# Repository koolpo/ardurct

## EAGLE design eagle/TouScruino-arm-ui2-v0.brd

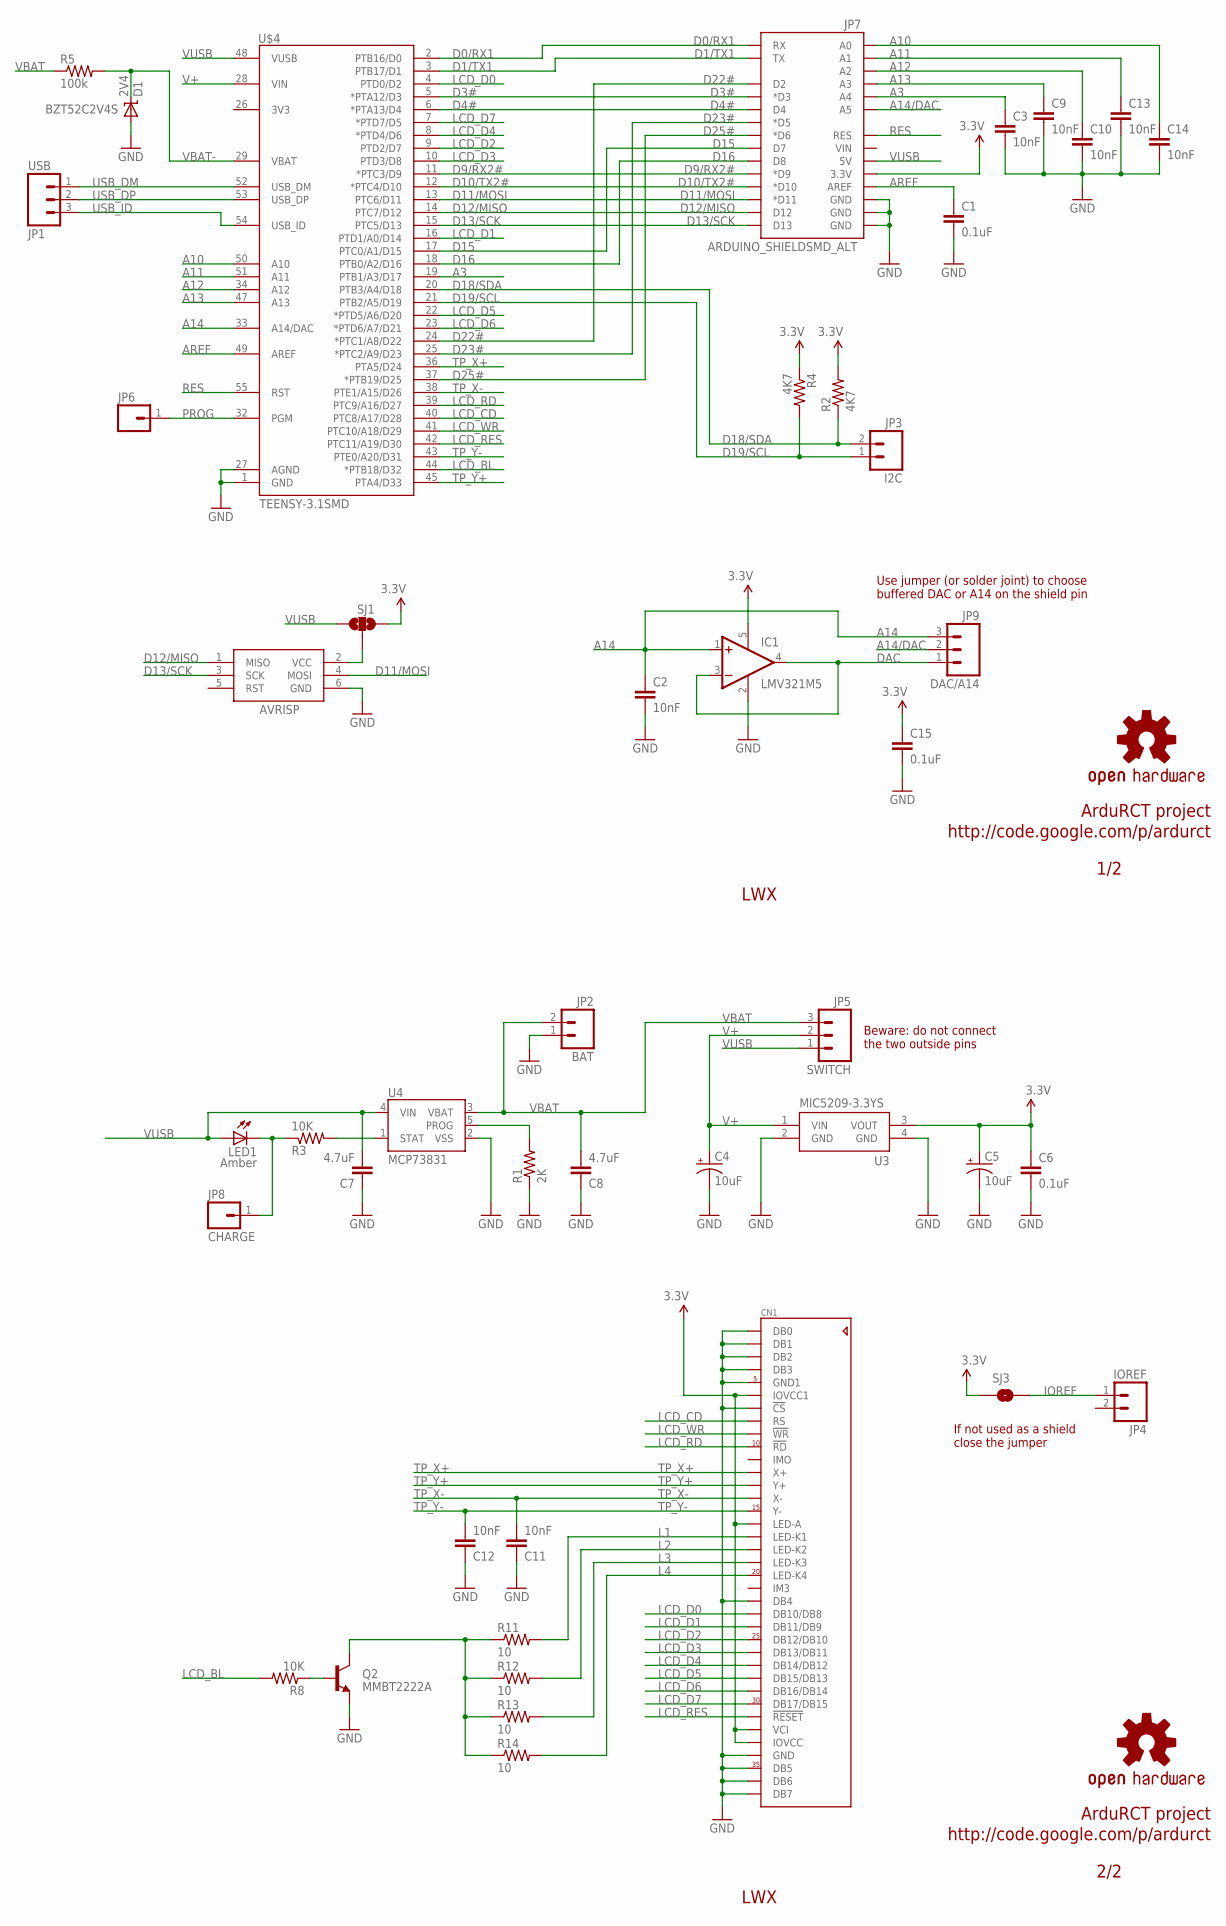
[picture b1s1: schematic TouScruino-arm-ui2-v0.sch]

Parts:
AVRISP: AVRISP; 2X3_SMD
C1, C6, C15: 0.1uF; 0805
C2, C3, C9, C10, C11, C12, C13, C14: 10nF; 0805
C4, C5: 10uF; EIA3216
C7, C8: 4.7uF; 0805
CN1: ILI9325_LCD1.0MM; ILI9325_28INCH_TS
D1: 2V4; SOD-323
IC1: LMV321M5; SOT23-5
JP1: USB; 1X03_SMD_ALT
JP2: BAT; JST-2-SMD
JP3: I2C; 1X02_SMD_ALT
JP4: IOREF; 1X02_SMD_ALT
JP5: SWITCH; 1X03_SMD_TH
JP6: M01SMD_TH; 1X01_SMD_TH
JP7: ARDUINO_SHIELDSMD_ALT; ARDUINO_SHIELD_SMD_ALT
JP8: CHARGE; 1X01_SMD
JP9: DAC/A14; 1X03_SMD_SJ
LED1: Amber; LED
Q2: MMBT2222A; SOT23-3
R1: 2K; 0805
R2, R4: 4K7; 0805
R3, R8: 10K; 0805
R5: 100k; 0805
R11, R12, R13, R14: 10; 0805
SJ1: SJ_2WAYS
SJ3: SOLDERJUMPERNO; SJ_2S-NO
U3: MIC5209-3.3YS; SOT223
U4: MCP73831; SOT23-5
U$3, U$5: OSHW-LOGOM; OSHW-LOGO-M
U$4: TEENSY-3.1SMD; TEENSY-3.1_HSMD

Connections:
3.3V: C5.A (+), C6.1, C15.1, CN1.6 (IOVCC1), CN1.16 (LED-A), CN1.32 (VCI), CN1.33 (IOVCC), IC1.5 (V+), JP7.3.3V, R2.2, R4.1, SJ1.3, SJ3.1, U3.3 (VOUT)
A3: C3.1, JP7.A4, U$4.19 (PTB1/A3/D17)
A10: C14.1, JP7.A0, U$4.50 (A10)
A11: C13.1, JP7.A1, U$4.51 (A11)
A12: C10.1, JP7.A2, U$4.34 (A12)
A13: C9.1, JP7.A3, U$4.47 (A13)
A14: C2.1, IC1.1 (+IN), JP9.3, U$4.33 (A14/DAC)
A14/DAC: JP7.A5, JP9.2
AREF: C1.1, JP7.AREF, U$4.49 (AREF)
D0/RX1: JP7.RX, U$4.2 (PTB16/D0)
D1/TX1: JP7.TX, U$4.3 (PTB17/D1)
D3#: JP7.D3 (*D3), U$4.5 (*PTA12/D3)
D4#: JP7.D4, U$4.6 (*PTA13/D4)
D9/RX2#: JP7.D9 (*D9), U$4.11 (*PTC3/D9)
D10/TX2#: JP7.D10 (*D10), U$4.12 (*PTC4/D10)
D11/MOSI: AVRISP.4 (MOSI), JP7.D11 (*D11), U$4.13 (PTC6/D11)
D12/MISO: AVRISP.1 (MISO), JP7.D12, U$4.14 (PTC7/D12)
D13/SCK: AVRISP.3 (SCK), JP7.D13, U$4.15 (PTC5/D13)
D15: JP7.D7, U$4.17 (PTC0/A1/D15)
D16: JP7.D8, U$4.18 (PTB0/A2/D16)
D18/SDA: JP3.2, R2.1, U$4.20 (PTB3/A4/D18)
D19/SCL: JP3.1, R4.2, U$4.21 (PTB2/A5/D19)
D22#: JP7.D2, U$4.24 (*PTC1/A8/D22)
D23#: JP7.D5 (*D5), U$4.25 (*PTC2/A9/D23)
D25#: JP7.D6 (*D6), U$4.37 (*PTB19/D25)
DAC: IC1.3 (-IN), IC1.4 (OUT), JP9.1
GND: AVRISP.6 (GND), C1.2, C2.2, C3.2, C4.C (-), C5.C (-), C6.2, C7.1, C8.1, C9.2, C10.2, C11.1, C12.1, C13.2, C14.2, C15.2, CN1.1 (DB0), CN1.2 (DB1), CN1.3 (DB2), CN1.4 (DB3), CN1.5 (GND1), CN1.7 (!CS), CN1.22 (DB4), CN1.34 (GND), CN1.35 (DB5), CN1.36 (DB6), CN1.37 (DB7), D1.2 (A), IC1.2 (V-), JP2.1, JP7.GND@0 (GND), JP7.GND@1 (GND), JP7.GND@2 (GND), Q2.2 (E), R1.1, U3.2 (GND), U3.4 (GND), U4.2 (VSS), U$4.1 (GND), U$4.27 (AGND)
IOREF: JP4.1, SJ3.2
L1: CN1.17 (LED-K1), R11.2
L2: CN1.18 (LED-K2), R12.2
L3: CN1.19 (LED-K3), R13.2
L4: CN1.20 (LED-K4), R14.2
LCD_BL: R8.2, U$4.44 (*PTB18/D32)
LCD_CD: CN1.8 (RS), U$4.40 (PTC8/A17/D28)
LCD_D0: CN1.23 (DB10/DB8), U$4.4 (PTD0/D2)
LCD_D1: CN1.24 (DB11/DB9), U$4.16 (PTD1/A0/D14)
LCD_D2: CN1.25 (DB12/DB10), U$4.9 (PTD2/D7)
LCD_D3: CN1.26 (DB13/DB11), U$4.10 (PTD3/D8)
LCD_D4: CN1.27 (DB14/DB12), U$4.8 (*PTD4/D6)
LCD_D5: CN1.28 (DB15/DB13), U$4.22 (*PTD5/A6/D20)
LCD_D6: CN1.29 (DB16/DB14), U$4.23 (*PTD6/A7/D21)
LCD_D7: CN1.30 (DB17/DB15), U$4.7 (*PTD7/D5)
LCD_RD: CN1.10 (!RD), U$4.39 (PTC9/A16/D27)
LCD_RES: CN1.31 (!RESET), U$4.42 (PTC11/A19/D30)
LCD_WR: CN1.9 (!WR), U$4.41 (PTC10/A18/D29)
unnamed: AVRISP.2 (VCC), SJ1.2
unnamed: Q2.1 (B), R8.1
unnamed: Q2.3 (C), R11.1, R12.1, R13.1, R14.1
unnamed: JP8.1, LED1.C1 (C), R3.1
unnamed: R3.2, U4.1 (STAT)
unnamed: R1.2, U4.5 (PROG)
PROG: JP6.1, U$4.32 (PGM)
RES: JP7.RES, U$4.55 (RST)
TP_X+: CN1.12 (X+), U$4.36 (PTA5/D24)
TP_X-: C11.2, CN1.14 (X-), U$4.38 (PTE1/A15/D26)
TP_Y+: CN1.13 (Y+), U$4.45 (PTA4/D33)
TP_Y-: C12.2, CN1.15 (Y-), U$4.43 (PTE0/A20/D31)
USB_DM: JP1.1, U$4.52 (USB_DM)
USB_DP: JP1.2, U$4.53 (USB_DP)
USB_ID: JP1.3, U$4.54 (USB_ID)
V+: C4.A (+), JP5.2, U3.1 (VIN), U$4.28 (VIN)
VBAT: C8.2, JP2.2, JP5.3, R5.1, U4.3 (VBAT)
VBAT-: D1.1 (C), R5.2, U$4.29 (VBAT)
VUSB: C7.2, JP5.1, JP7.5V, LED1.A1 (A), SJ1.1, U4.4 (VIN), U$4.48 (VUSB)

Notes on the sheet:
LWX
1/2
2/2
Beware: do not connect the two outside pins
If not used as a shield close the jumper
ArduRCT project
http://code.google.com/p/ardurct
Use jumper (or solder joint) to choose buffered DAC or A14 on the shield pin
BZT52C2V4S

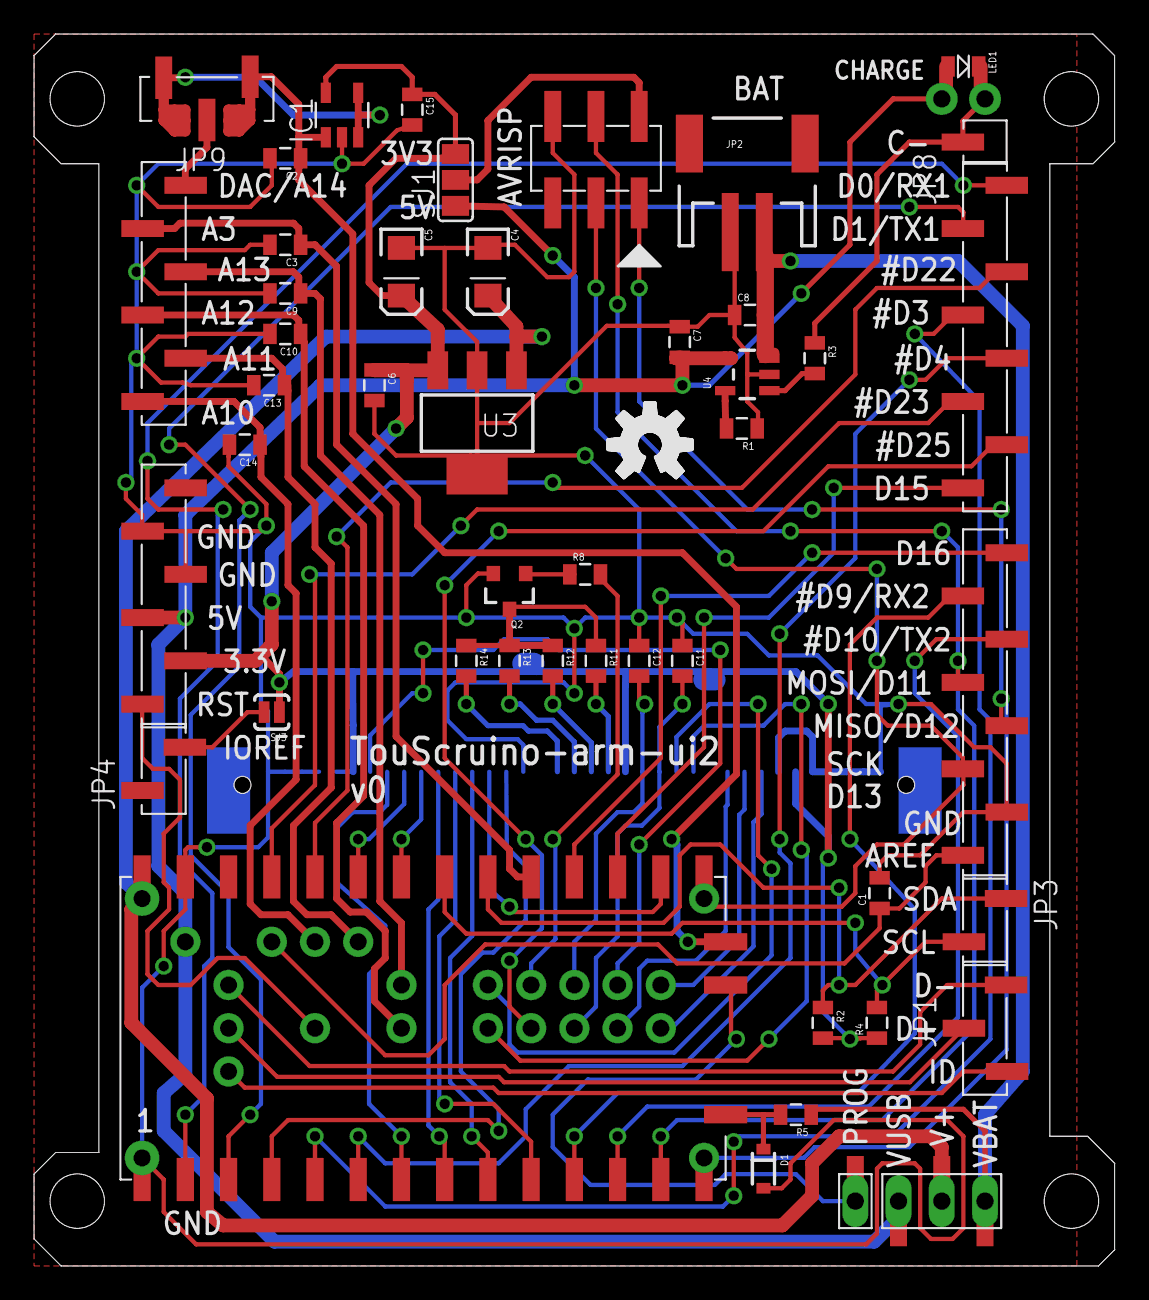
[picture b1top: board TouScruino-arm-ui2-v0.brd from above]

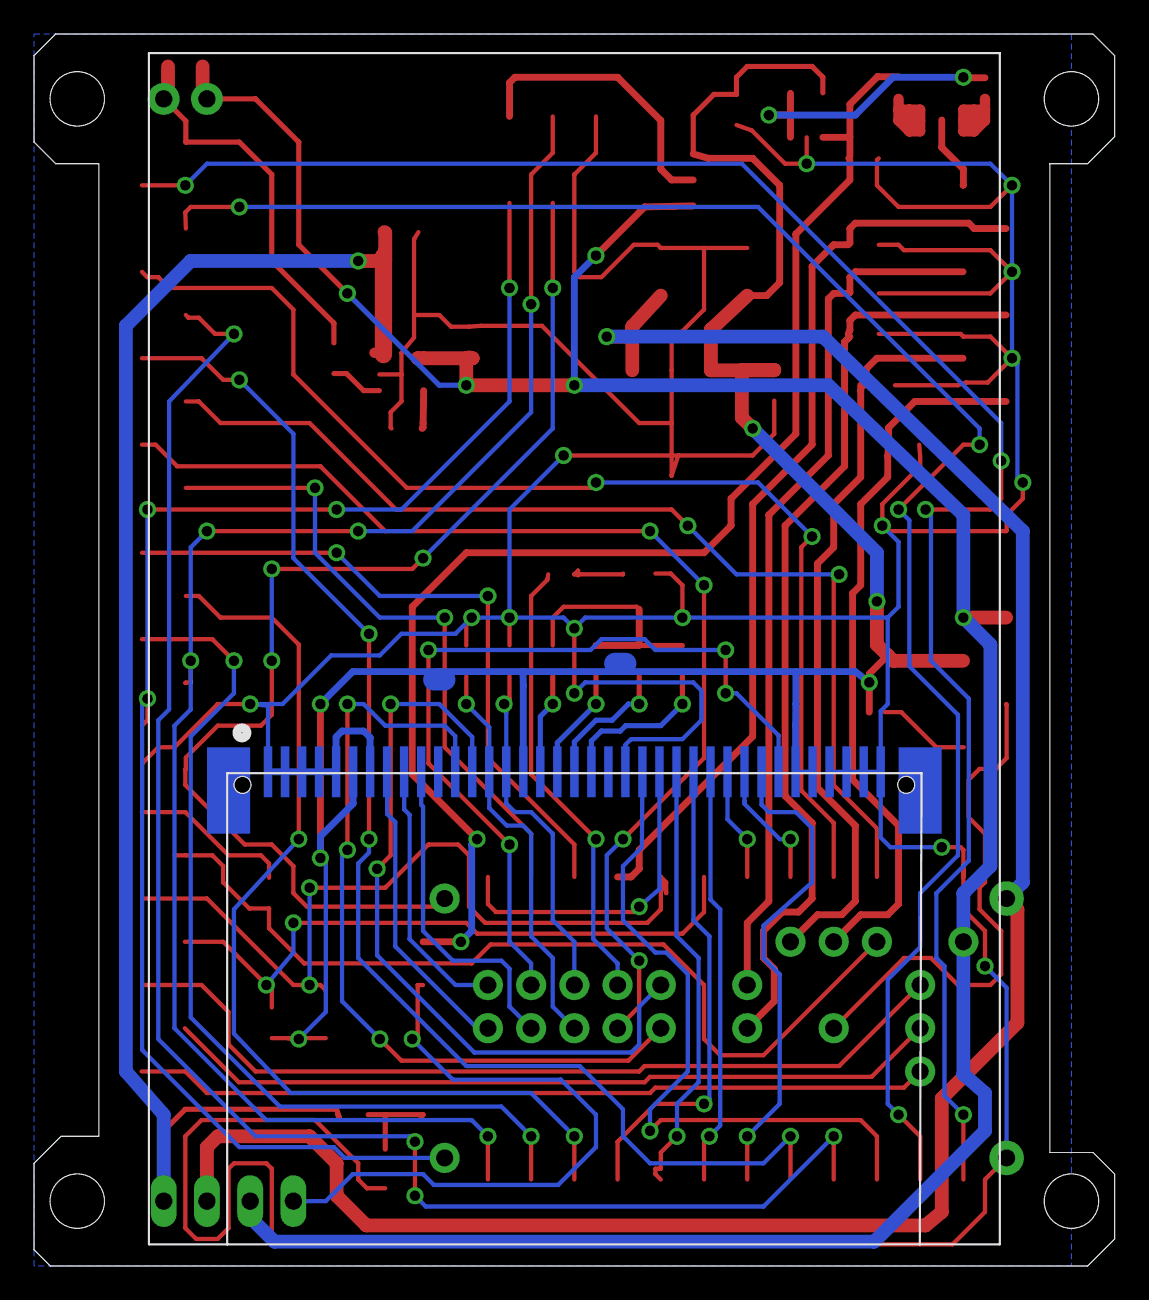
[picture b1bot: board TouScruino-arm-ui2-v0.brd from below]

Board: 2 copper layers, 63.5 x 72.4 mm, 47 parts (3 on the bottom side), 64 nets.

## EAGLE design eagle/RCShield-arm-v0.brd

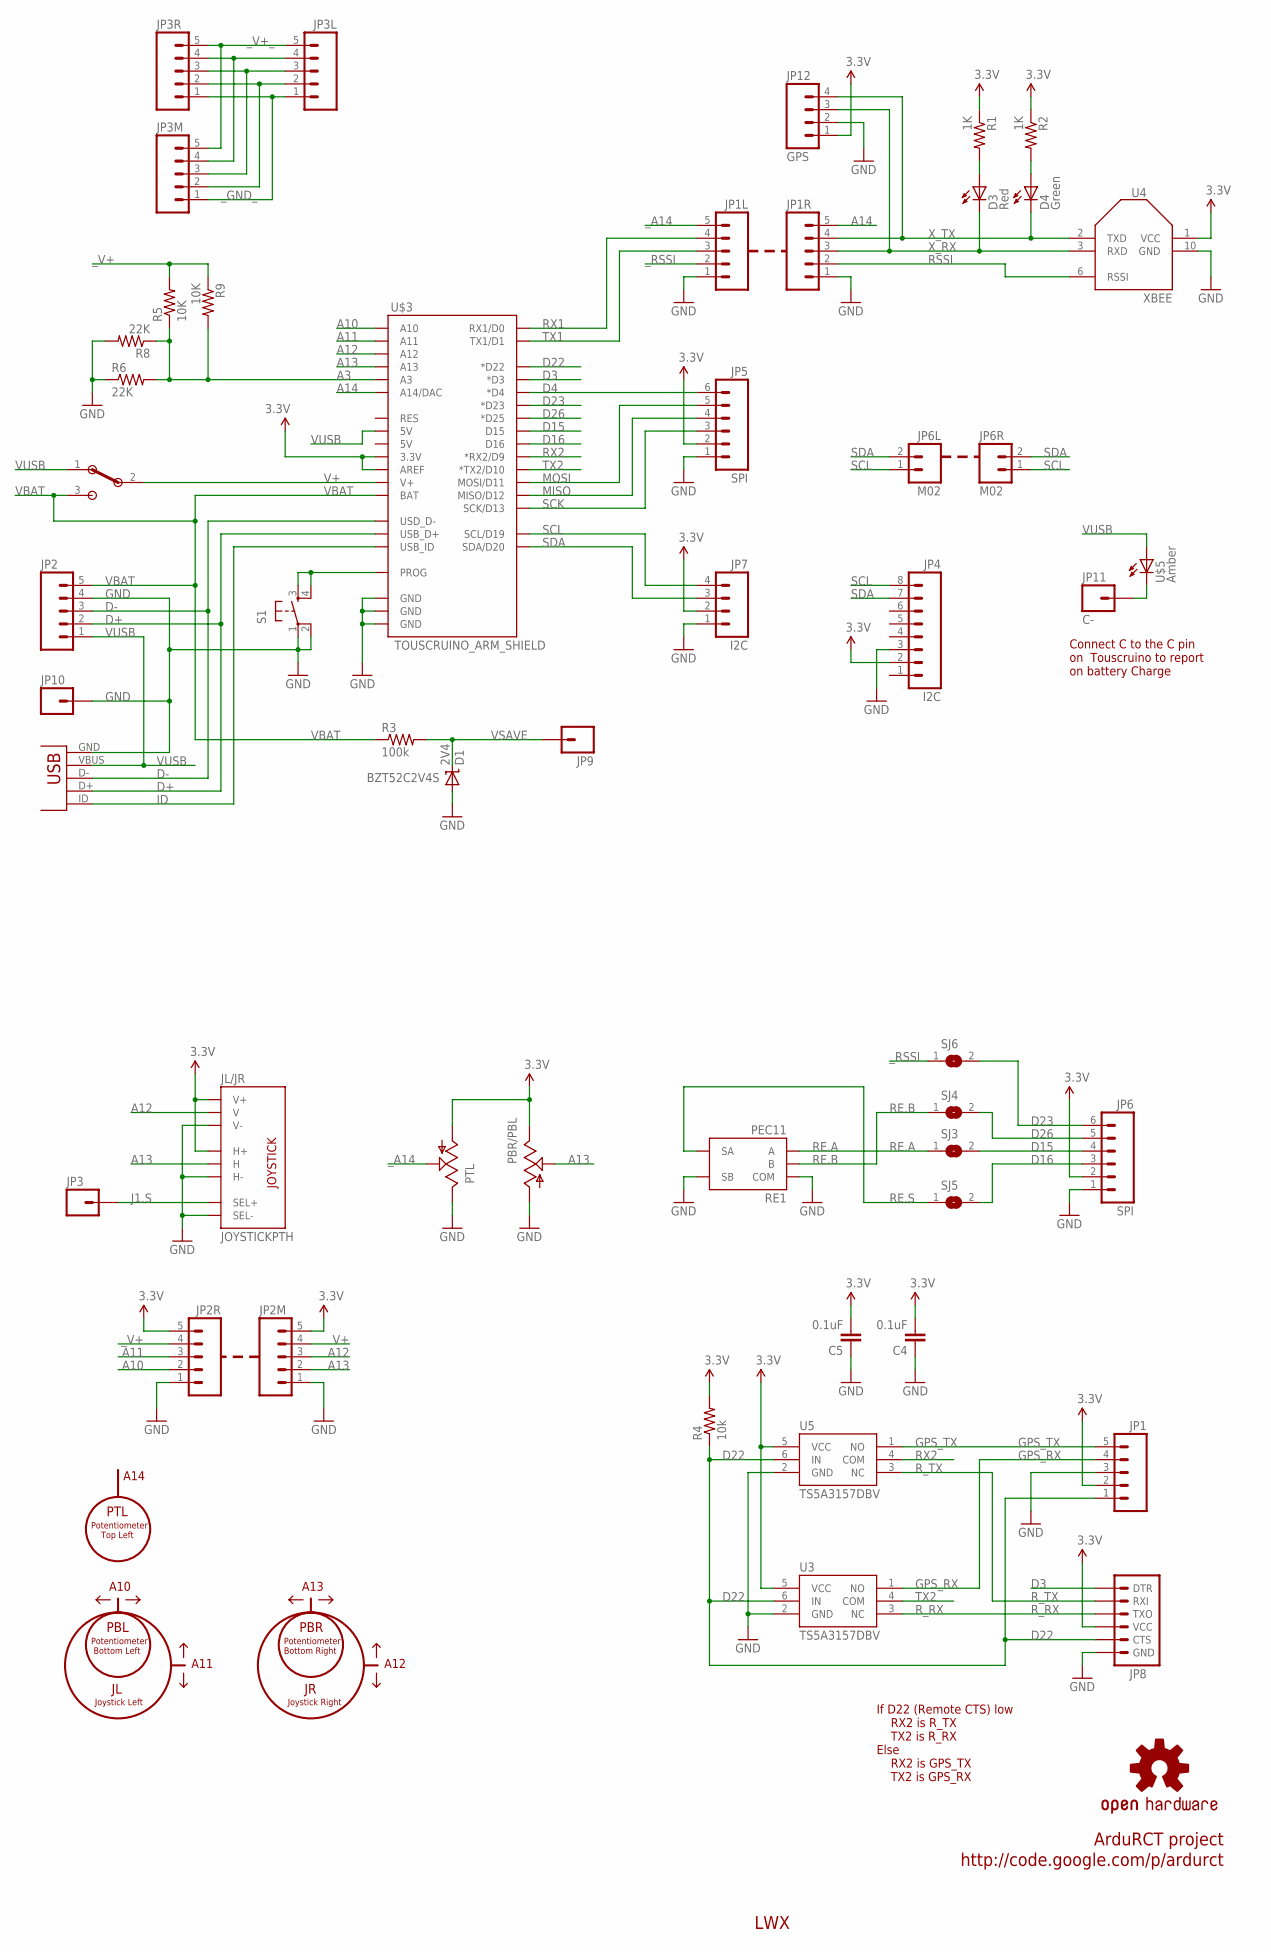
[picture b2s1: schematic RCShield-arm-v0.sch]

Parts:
C4, C5: 0.1uF; 0805
D1: 2V4; SOD-323
D3: Red; LED
D4: Green; LED
JL/JR: JOYSTICKPTH; JOYSTICK
JP1, JP2: M05PTH; 1X05
JP1L, JP1R, JP2M, JP2R, JP3L, JP3M, JP3R: M05; 2+3
JP3, JP9, JP10: M01PTH; 1X01
JP4: I2C; 1X08
JP5, JP6: SPI; 1X06
JP6L, JP6R: M02; 1X02
JP7: I2C; 1X04
JP8: ARDUINO_SERIAL_PROGRAM; 1X06_F
JP11: C-; 1X01
JP12: GPS; 1X04
PBR/PBL: POT; ALPS_POT
PTL: POT; ALPS_POT
R1, R2: 1K; 0805
R3: 100k; 0805
R4: 10k; 0805
R5: 10K; 0805
R6: 22K; 0805
R8: 22K; 0207/7
R9: 10K; 0207/7
RE1: PEC11
S1: TAC_SWITCHPTH; TACTILE-PTH
S4: EG1224
SJ3, SJ4, SJ5, SJ6: SJ
U3, U5: TS5A3157DBV; SOT23-6
U4: XBEE; XBEE-SMD
U$1: OSHW-LOGOM; OSHW-LOGO-M
U$3: TOUSCRUINO_ARM_SHIELD; TOUSCRUINO_ARM_SHIELD_SPLIT
U$5: Amber; LED
X1: USB; USB-MICROB

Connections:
3.3V: C4.2, C5.2, JL/JR.H1 (H+), JL/JR.V1 (V+), JP1.2, JP2M.5, JP2R.5, JP4.2, JP5.2, JP6.2, JP7.2, JP8.4 (VCC), JP12.1, PBR/PBL.P$1 (E), PTL.P$3 (A), R1.1, R2.1, R4.2, U3.5 (VCC), U4.1 (VCC), U5.5 (VCC), U$3.3.3V, U$3.AREF
A3: R5.1, R6.2, R8.1, R9.2, U$3.A3
A10: JP2R.2, U$3.A10
A11: JP2R.3, U$3.A11
A12: JL/JR.V2 (V), JP2M.3, U$3.A12
A13: JL/JR.H2 (H), JP2M.2, PBR/PBL.P$2 (S), U$3.A13
A14: JP1R.5, U$3.A14 (A14/DAC)
C-: JP11.1, U$5.C1 (C)
D3: JP8.1 (DTR), U$3.D3 (*D3)
D4: JP5.6, U$3.D4 (*D4)
D15: JP6.4, SJ3.2, U$3.D15
D16: JP6.3, SJ5.2, U$3.D16
D22: JP1.1, JP8.5 (CTS), R4.1, U3.6 (IN), U5.6 (IN), U$3.D22 (*D22)
D23: JP6.6, SJ6.2, U$3.D23 (*D23)
D26: JP6.5, SJ4.2, U$3.D25 (*D25)
D+: JP2.2, U$3.USB_D+, X1.D+
D-: JP2.3, U$3.USB_D- (USD_D-), X1.D-
GND: C4.1, C5.1, D1.2 (A), JL/JR.B2A (SEL-), JL/JR.H3 (H-), JL/JR.V3 (V-), JP1.3, JP1L.1, JP1R.1, JP2.4, JP2M.1, JP2R.1, JP4.3, JP5.1, JP6.1, JP7.1, JP8.6 (GND), JP10.1, JP12.2, PBR/PBL.P$3 (A), PTL.P$1 (E), R6.1, R8.2, RE1.C (COM), RE1.S2 (SB), S1.1, S1.2, U3.2 (GND), U4.10 (GND), U5.2 (GND), U$3.GND@0 (GND), U$3.GND@1 (GND), U$3.GND@2 (GND), X1.GND
GPS_RX: JP1.4, U3.1 (NO)
GPS_TX: JP1.5, U5.1 (NO)
ID: U$3.USB_ID, X1.ID
J1.S: JL/JR.B1A (SEL+), JP3.1
MISO: JP5.4, U$3.D12 (MISO/D12)
MOSI: JP5.5, U$3.D11 (MOSI/D11)
unnamed: S1.3, S1.4, U$3.PROG
unnamed: JP3L.4, JP3M.4, JP3R.4
unnamed: JP3L.3, JP3M.3, JP3R.3
unnamed: JP3L.2, JP3M.2, JP3R.2
unnamed: D3.A1 (A), R1.2
unnamed: D4.A1 (A), R2.2
RE.A: RE1.A, SJ3.1
RE.B: RE1.B, SJ4.1
RE.S: RE1.S1 (SA), SJ5.1
RSSI: JP1R.2, U4.6 (RSSI)
RX1: JP1L.4, U$3.RX1/D0
RX2: U5.4 (COM), U$3.D9 (*RX2/D9)
R_RX: JP8.3 (TXO), U3.3 (NC)
R_TX: JP8.2 (RXI), U5.3 (NC)
SCK: JP5.3, U$3.D13 (SCK/D13)
SCL: JP4.8, JP6L.1, JP6R.1, JP7.4, U$3.SCL (SCL/D19)
SDA: JP4.7, JP6L.2, JP6R.2, JP7.3, U$3.SDA (SDA/D20)
TX1: JP1L.3, U$3.TX1/D1
TX2: U3.4 (COM), U$3.D10 (*TX2/D10)
V+: JP2M.4, S4.2, U$3.V+
VBAT: JP2.5, R3.1, S4.3, U$3.BAT
VSAVE: D1.1 (C), JP9.1, R3.2
VUSB: JP2.1, S4.1, U$3.5V@1 (5V), U$5.A1 (A), X1.VBUS
X_RX: D3.C1 (C), JP1R.3, JP12.3, U4.3 (RXD)
X_TX: D4.C1 (C), JP1R.4, JP12.4, U4.2 (TXD)
_A14: JP1L.5, PTL.P$2 (S)
_GND_: JP3L.1, JP3M.1, JP3R.1
_RSSI: JP1L.2, SJ6.1
_V+: JP2R.4, R5.2, R9.1
_V+_: JP3L.5, JP3M.5, JP3R.5

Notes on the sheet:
ArduRCT project
http://code.google.com/p/ardurct
If D22 (Remote CTS) low RX2 is R_TX TX2 is R_RX Else RX2 is GPS_TX TX2 is GPS_RX
LWX
PBL
Potentiometer Bottom Left
Joystick Left
PTL
Potentiometer Top Left
A14
A10
A11
PBR
Potentiometer Bottom Right
Joystick Right
A13
A12
Connect C to the C pin on Touscruino to report on battery Charge
BZT52C2V4S

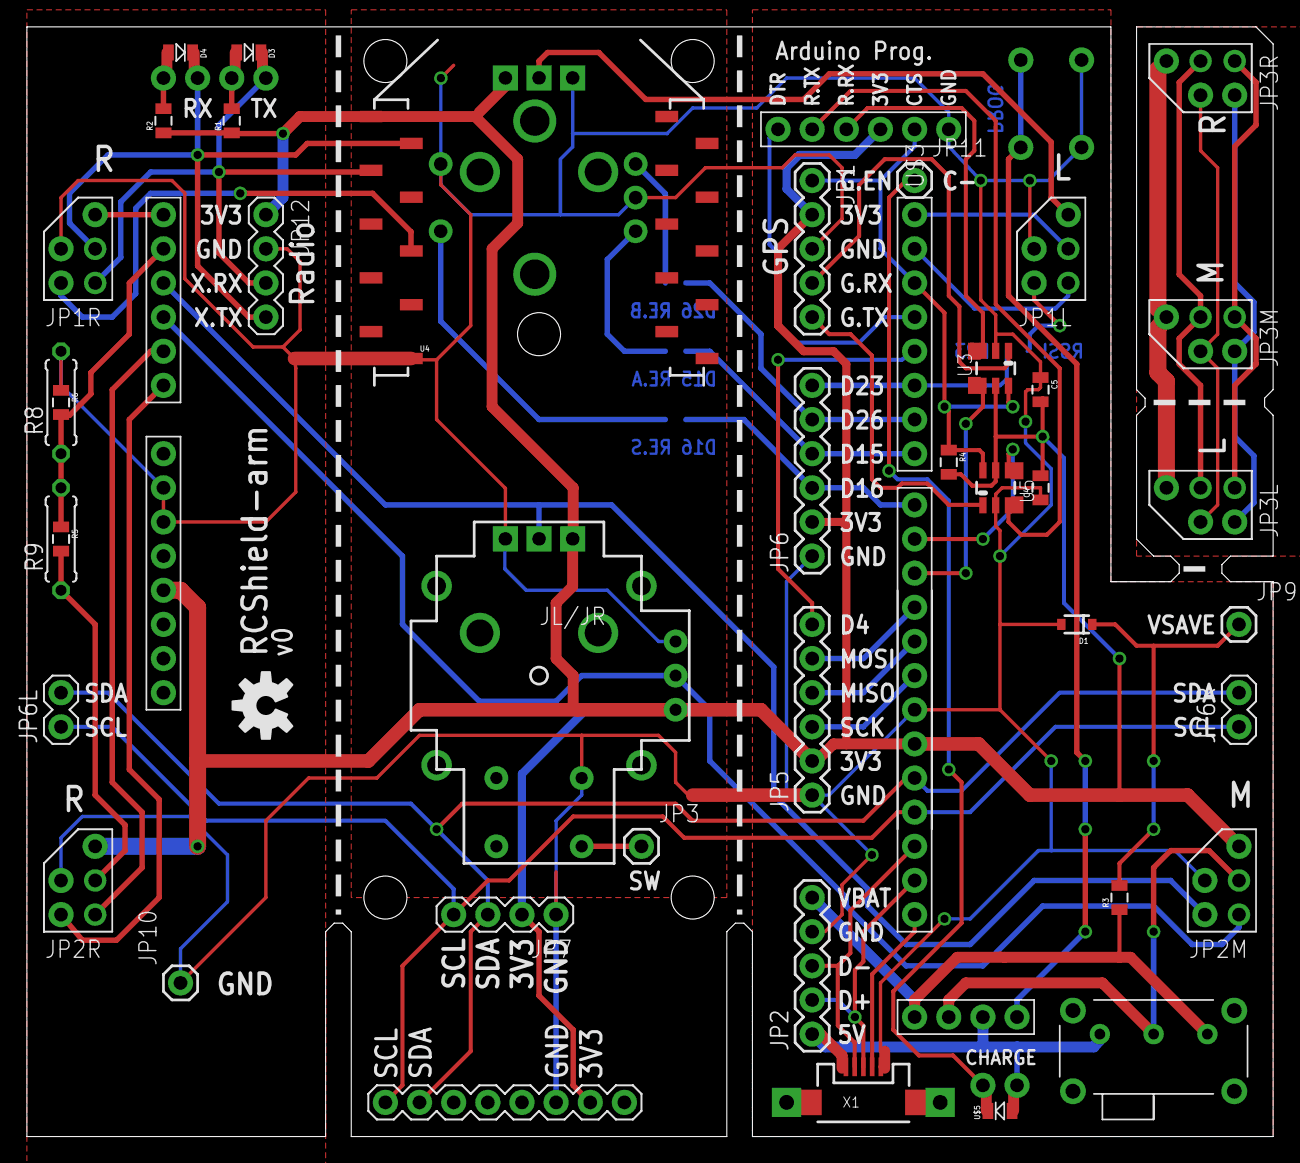
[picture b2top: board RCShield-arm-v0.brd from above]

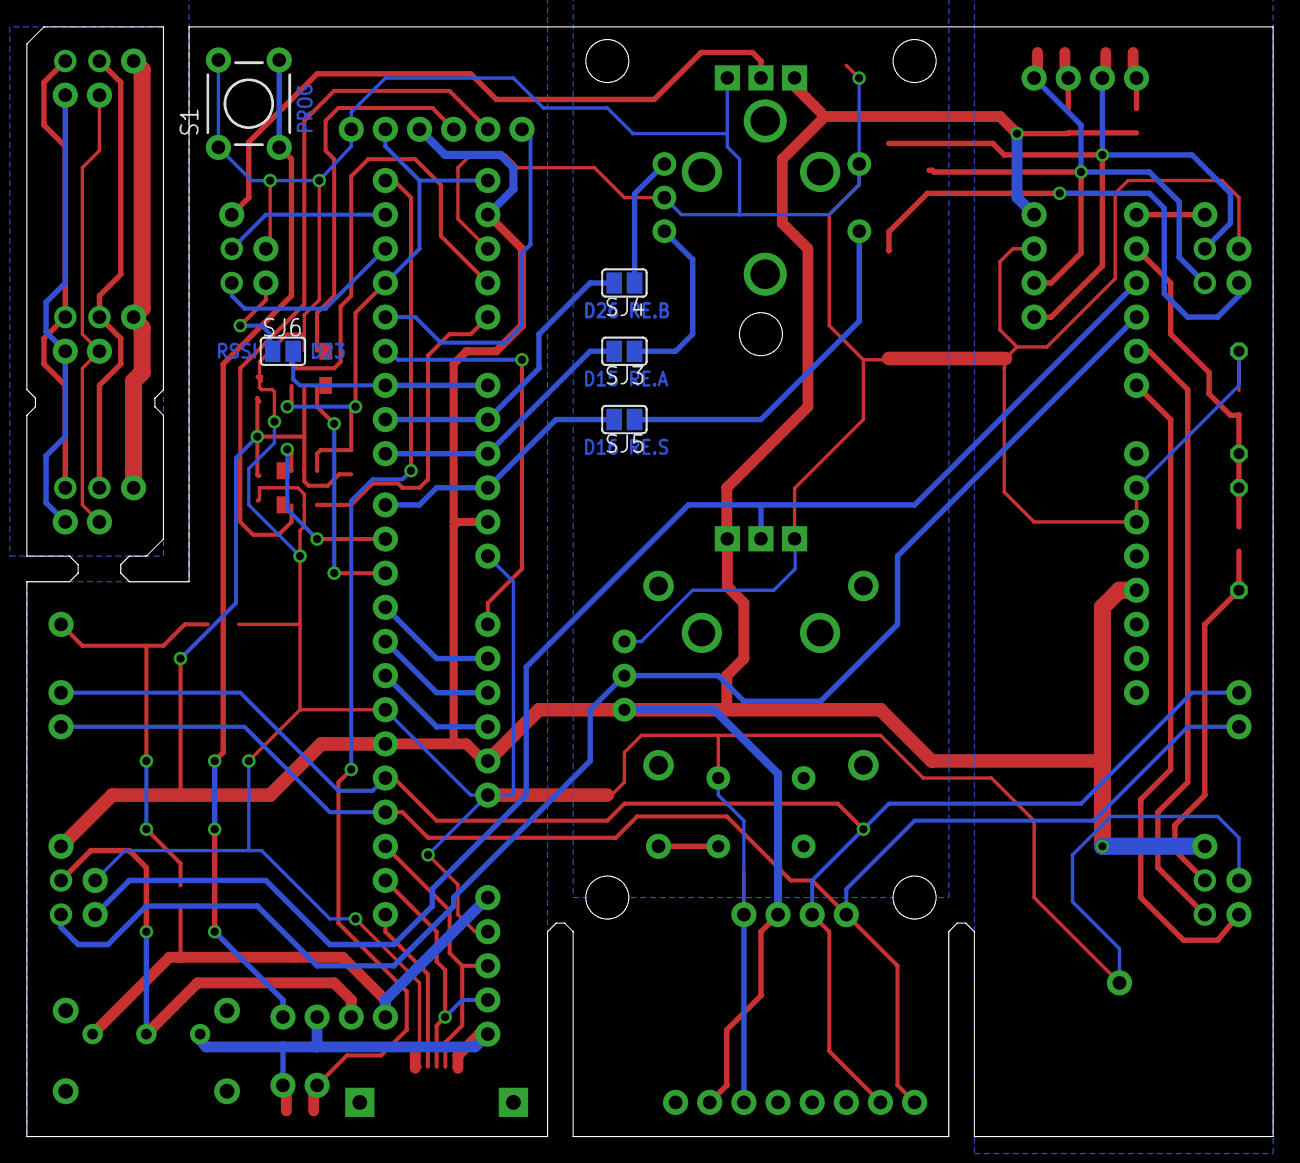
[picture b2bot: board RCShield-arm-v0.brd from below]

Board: 2 copper layers, 92.7 x 82.5 mm, 51 parts (5 on the bottom side), 54 nets.

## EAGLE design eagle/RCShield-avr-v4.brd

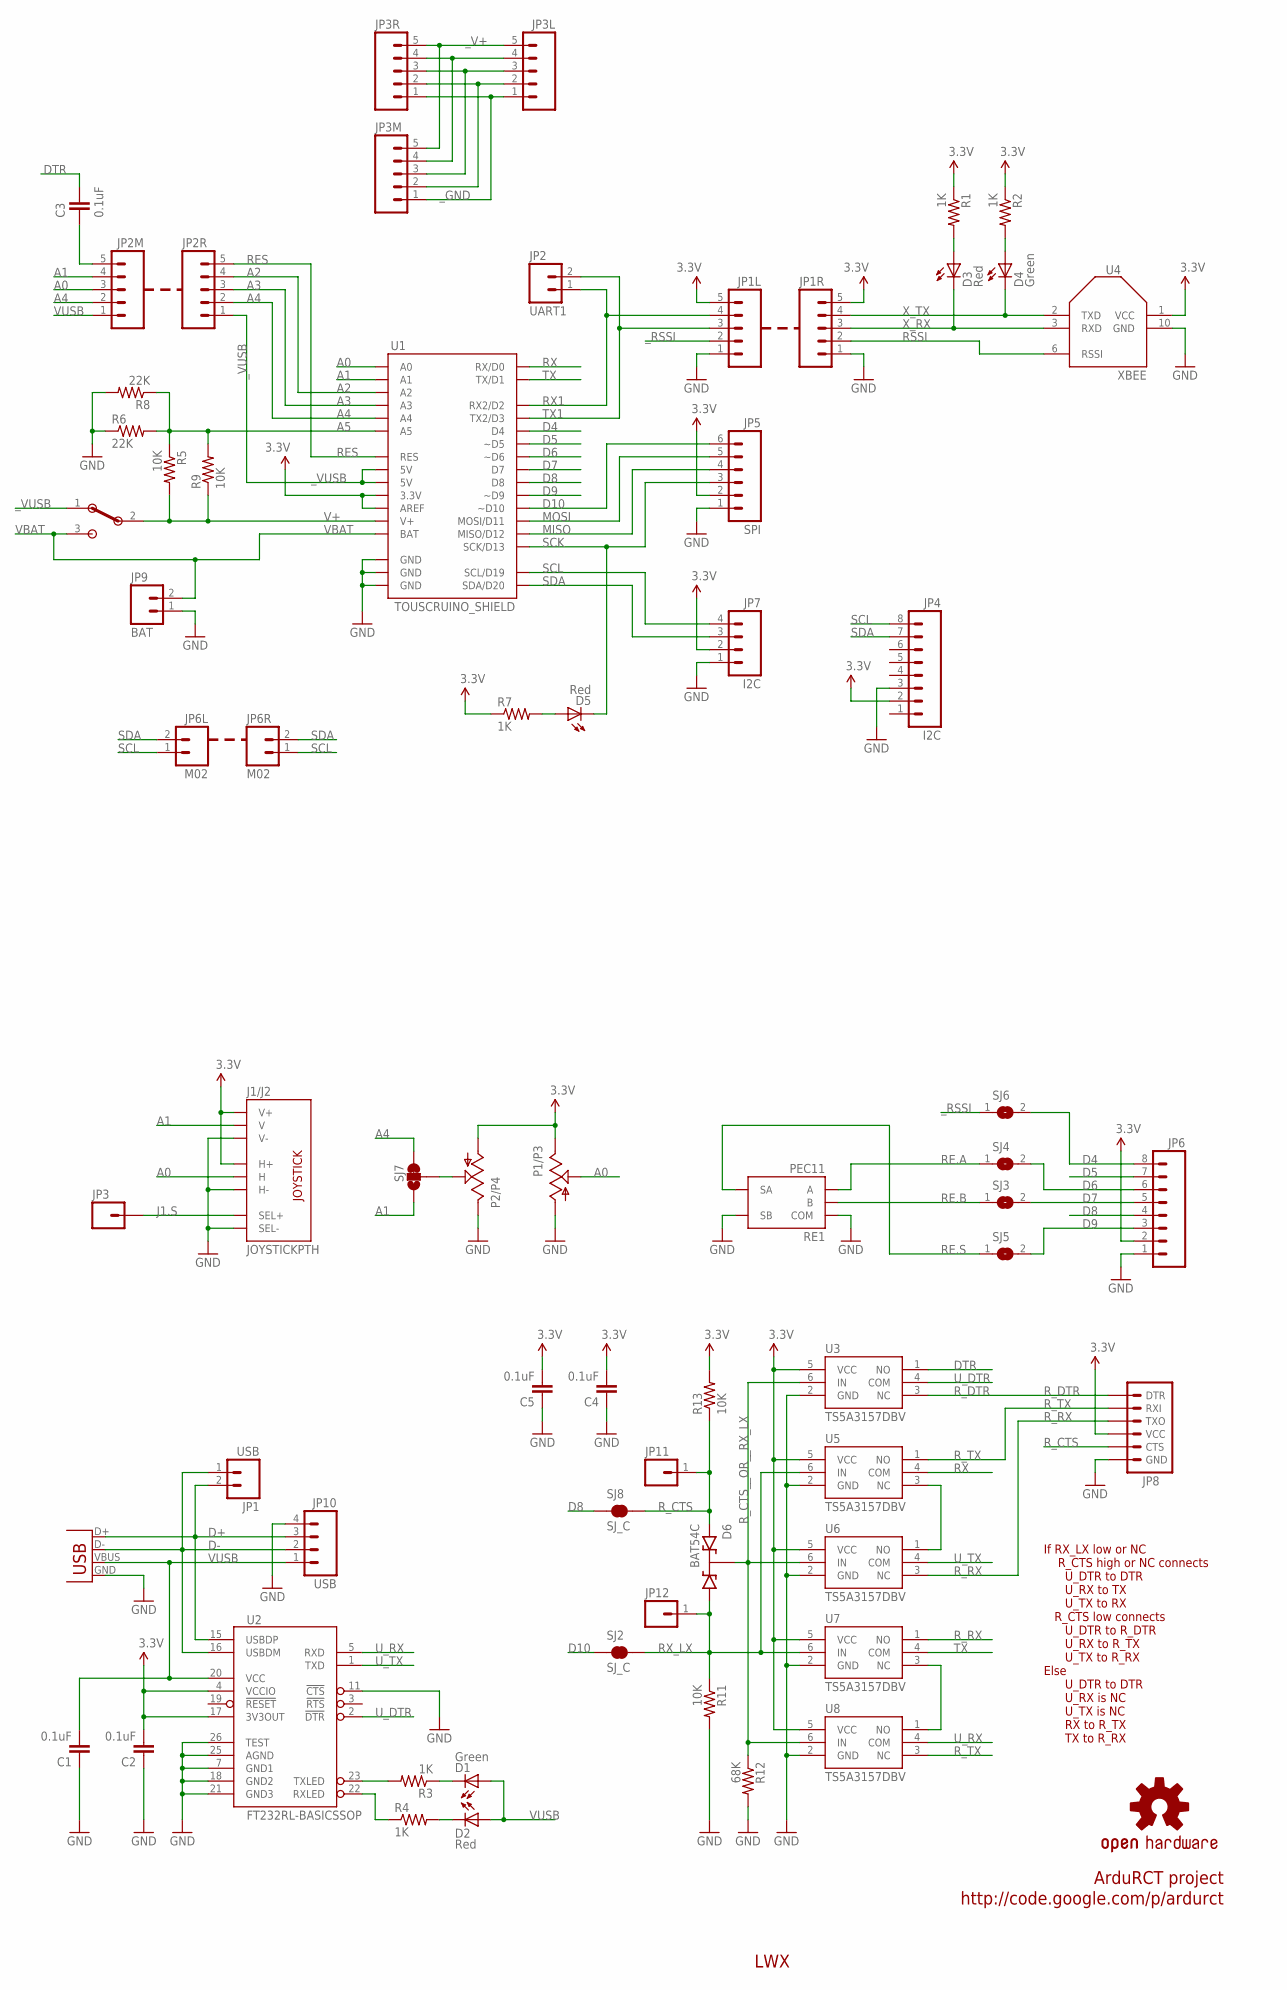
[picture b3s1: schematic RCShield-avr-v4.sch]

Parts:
C1, C2, C3, C4, C5: 0.1uF; 0805
D1, D4: Green; LED
D2, D3, D5: Red; LED
D6: BAT54C; SOT23-3
J1/J2: JOYSTICKPTH; JOYSTICK
JP1: USB; 1X02
JP1L, JP1R, JP2M, JP2R, JP3L, JP3M, JP3R: M05; 2+3
JP2: UART1; 1X02
JP3: M01PTH; 1X01
JP4: I2C; 1X08
JP5: SPI; 1X06
JP6: M08; 1X08
JP6L, JP6R: M02; 1X02
JP7: I2C; 1X04
JP8: ARDUINO_SERIAL_PROGRAM; 1X06_F
JP9: BAT; 1X02
JP10: USB; 1X04
JP11, JP12: M01SMALL; 1X01_S
P1/P3, P2/P4: POT; ALPS_POT
R1, R2, R3, R4, R7: 1K; 0805
R5, R11, R13: 10K; 0805
R6: 22K; 0805
R8: 22K; 0207/7
R9: 10K; 0207/7
R12: 68K; 0805
RE1: PEC11
S4: EG1224
SJ2, SJ8: SJ_C
SJ3, SJ4, SJ5, SJ6: SJ
SJ7: SJ_2WAYS_1-2W; SJ_2WAYS_1-2
U1: TOUSCRUINO_SHIELD; TOUSCRUINO_SHIELD_SPLIT
U2: FT232RL-BASICSSOP; SSOP28DB
U3, U5, U6, U7, U8: TS5A3157DBV; SOT23-6
U4: XBEE; XBEE-SMD
U$1: OSHW-LOGOM; OSHW-LOGO-M
X1: USB; USB-MICROB

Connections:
3.3V: C2.2, C4.2, C5.2, J1/J2.H1 (H+), J1/J2.V1 (V+), JP1L.5, JP1R.5, JP4.2, JP5.2, JP6.2, JP7.2, JP8.4 (VCC), P1/P3.P$1 (E), P2/P4.P$3 (A), R1.1, R2.1, R7.1, R13.2, U1.3.3V, U1.AREF, U2.4 (VCCIO), U2.17 (3V3OUT), U3.5 (VCC), U4.1 (VCC), U5.5 (VCC), U6.5 (VCC), U7.5 (VCC), U8.5 (VCC)
A0: J1/J2.H2 (H), JP2M.3, P1/P3.P$2 (S), U1.A0
A1: J1/J2.V2 (V), JP2M.4, SJ7.3, U1.A1
A2: JP2R.4, U1.A2
A3: JP2R.3, U1.A3
A4: JP2M.2, JP2R.2, SJ7.1, U1.A4
A5: R5.1, R6.2, R8.1, R9.2, U1.A5
D4: JP6.8, SJ6.2, U1.D4
D5: JP6.7, U1.D5 (~D5)
D6: JP6.6, SJ4.2, U1.D6 (~D6)
D7: JP6.5, SJ3.2, U1.D7
D8: JP6.4, SJ8.1, U1.D8
D9: JP6.3, SJ5.2, U1.D9 (~D9)
D10: JP5.6, SJ2.1, U1.D10 (~D10)
D+: JP1.2, JP10.3, U2.15 (USBDP), X1.D+
D-: JP1.1, JP10.2, U2.16 (USBDM), X1.D-
DTR: C3.1, U3.1 (NO)
GND: C1.1, C2.1, C4.1, C5.1, J1/J2.B2A (SEL-), J1/J2.H3 (H-), J1/J2.V3 (V-), JP1L.1, JP1R.1, JP4.3, JP5.1, JP6.1, JP7.1, JP8.6 (GND), JP9.1, JP10.4, P1/P3.P$3 (A), P2/P4.P$1 (E), R6.1, R8.2, R11.2, R12.2, RE1.C (COM), RE1.S2 (SB), U1.GND@0 (GND), U1.GND@1 (GND), U1.GND@2 (GND), U2.7 (GND1), U2.11 (!CTS), U2.18 (GND2), U2.21 (GND3), U2.25 (AGND), U2.26 (TEST), U3.2 (GND), U4.10 (GND), U5.2 (GND), U6.2 (GND), U7.2 (GND), U8.2 (GND), X1.GND
J1.S: J1/J2.B1A (SEL+), JP3.1
MISO: JP5.4, U1.D12 (MISO/D12)
MOSI: JP5.5, U1.D11 (MOSI/D11)
unnamed: C3.2, JP2M.5
unnamed: JP3L.4, JP3M.4, JP3R.4
unnamed: JP3L.3, JP3M.3, JP3R.3
unnamed: JP3L.2, JP3M.2, JP3R.2
unnamed: P2/P4.P$2 (S), SJ7.2
unnamed: D5.A1 (A), R7.2
unnamed: U7.3 (NC), U8.1 (NO)
unnamed: U5.3 (NC), U6.1 (NO)
unnamed: D3.A1 (A), R1.2
unnamed: R3.2, U2.23 (TXLED)
unnamed: R4.1, U2.22 (RXLED)
unnamed: D4.A1 (A), R2.2
RE.A: RE1.A, SJ4.1
RE.B: RE1.B, SJ3.1
RE.S: RE1.S1 (SA), SJ5.1
RES: JP2R.5, U1.RES
RSSI: JP1R.2, U4.6 (RSSI)
RX: U1.RX (RX/D0), U5.4 (COM)
RX1: JP1L.4, JP2.1, U1.D2 (RX2/D2)
RX_LX: D6.1 (A1), JP12.1, R11.1, SJ2.2, U5.6 (IN), U7.6 (IN)
R_CTS: D6.2 (A2), JP8.5 (CTS), JP11.1, R13.1, SJ8.2
R_CTS__OR__RX_LX: D6.3 (K), R12.1, U3.6 (IN), U6.6 (IN), U8.6 (IN)
R_DTR: JP8.1 (DTR), U3.3 (NC)
R_RX: JP8.3 (TXO), U6.3 (NC), U7.1 (NO)
R_TX: JP8.2 (RXI), U5.1 (NO), U8.3 (NC)
SCK: D5.C1 (C), JP5.3, U1.D13 (SCK/D13)
SCL: JP4.8, JP6L.1, JP6R.1, JP7.4, U1.SCL (SCL/D19)
SDA: JP4.7, JP6L.2, JP6R.2, JP7.3, U1.SDA (SDA/D20)
TX: U1.TX (TX/D1), U7.4 (COM)
TX1: JP1L.3, JP2.2, U1.D3 (TX2/D3)
U_DTR: U2.2 (!DTR), U3.4 (COM)
U_RX: U2.5 (RXD), U8.4 (COM)
U_RX_LED: D2.C1 (C), R4.2
U_TX: U2.1 (TXD), U6.4 (COM)
U_TX_LED: D1.C1 (C), R3.1
V+: R5.2, R9.1, S4.2, U1.V+
VBAT: JP9.2, S4.3, U1.BAT
VUSB: C1.2, D1.A1 (A), D2.A1 (A), JP2M.1, JP10.1, U2.20 (VCC), X1.VBUS
X_RX: D3.C1 (C), JP1R.3, U4.3 (RXD)
X_TX: D4.C1 (C), JP1R.4, U4.2 (TXD)
_GND: JP3L.1, JP3M.1, JP3R.1
_RSSI: JP1L.2, SJ6.1
_V+: JP3L.5, JP3M.5, JP3R.5
_VUSB: JP2R.1, S4.1, U1.5V@0 (5V), U1.5V@1 (5V)

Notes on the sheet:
ArduRCT project
http://code.google.com/p/ardurct
If RX_LX low or NC R_CTS high or NC connects U_DTR to DTR U_RX to TX U_TX to RX R_CTS low connects U_DTR to R_DTR U_RX to R_TX U_TX to R_RX Else U_DTR to DTR U_RX is NC U_TX is NC RX to R_TX TX to R_RX
LWX

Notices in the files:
parts and their libraries:
SparkFun-DiscreteSemi: Licensing: CC v3.0 Share-Alike You are welcome to use this library for commercial purposes.
